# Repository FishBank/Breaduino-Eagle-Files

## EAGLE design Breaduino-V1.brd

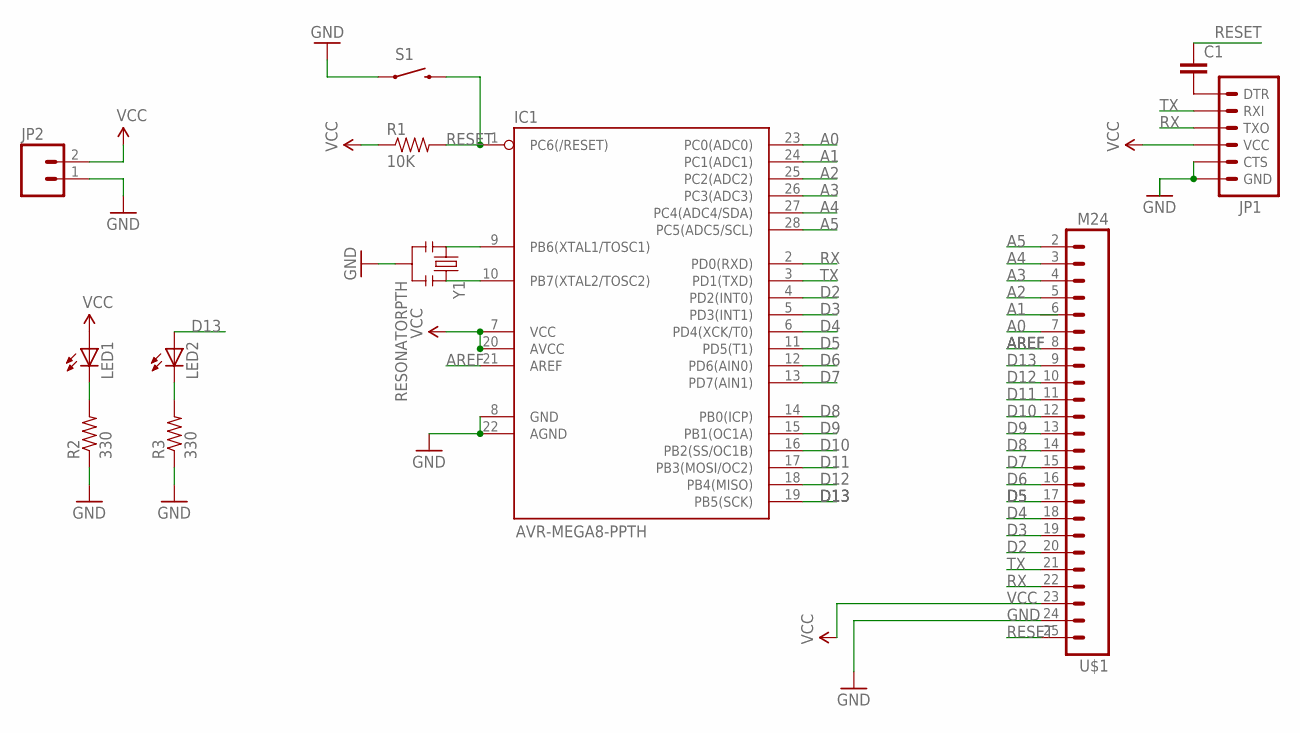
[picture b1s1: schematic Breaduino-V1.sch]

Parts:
C1: CAPPTH; CAP-PTH-SMALL
IC1: AVR-MEGA8-PPTH; DIL28-3
JP1: ARDUINO_SERIAL_PROGRAMPTH; 1X06
JP2: M02JST-PTH-2; JST-2-PTH
LED1, LED2: LED3MM
R1: 10K; AXIAL-0.3
R2, R3: 330; AXIAL-0.3
S1: SWITCH-MOMENTARY-2PTH; TACTILE-PTH
U$1: M24; 1X24
Y1: RESONATORPTH; RESONATOR-PTH

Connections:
A0: IC1.23 (PC0(ADC0)), U$1.7
A1: IC1.24 (PC1(ADC1))
A2: IC1.25 (PC2(ADC2)), U$1.5
A3: IC1.26 (PC3(ADC3)), U$1.4
A4: IC1.27 (PC4(ADC4/SDA)), U$1.3
A5: IC1.28 (PC5(ADC5/SCL)), U$1.2
AREF: IC1.21 (AREF), U$1.8
D2: IC1.4 (PD2(INT0)), U$1.20
D3: IC1.5 (PD3(INT1)), U$1.19
D4: IC1.6 (PD4(XCK/T0)), U$1.18
D5: IC1.11 (PD5(T1)), U$1.17
D6: IC1.12 (PD6(AIN0)), U$1.16
D7: IC1.13 (PD7(AIN1)), U$1.15
D8: IC1.14 (PB0(ICP)), U$1.14
D9: IC1.15 (PB1(OC1A)), U$1.13
D10: IC1.16 (PB2(SS/OC1B)), U$1.12
D11: IC1.17 (PB3(MOSI/OC2)), U$1.11
D12: IC1.18 (PB4(MISO)), U$1.10
D13: IC1.19 (PB5(SCK)), LED2.A, U$1.9
GND: IC1.8 (GND), JP1.5 (CTS), JP1.6 (GND), JP2.1, R2.P$1 (1), R3.P$1 (1), S1.1, U$1.24, Y1.2
unnamed: LED1.K (C), R2.P$2 (2)
unnamed: LED2.K (C), R3.P$2 (2)
unnamed: IC1.9 (PB6(XTAL1/TOSC1)), Y1.1
unnamed: IC1.10 (PB7(XTAL2/TOSC2)), Y1.3
unnamed: C1.2, JP1.1 (DTR)
RESET: C1.1, IC1.1 (PC6(/RESET)), R1.P$2 (2), S1.3 (2), U$1.25
RX: IC1.2 (PD0(RXD)), JP1.3 (TXO), U$1.22
TX: IC1.3 (PD1(TXD)), JP1.2 (RXI), U$1.21
VCC: IC1.7 (VCC), IC1.20 (AVCC), JP1.4 (VCC), JP2.2, LED1.A, R1.P$1 (1), U$1.23

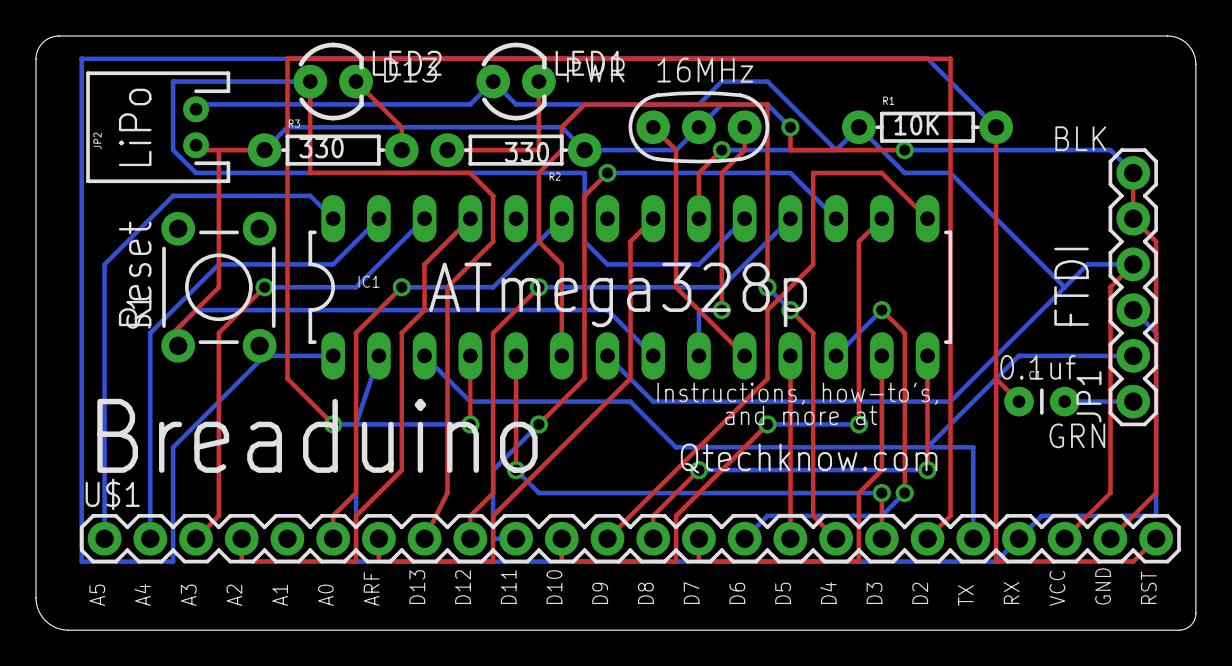
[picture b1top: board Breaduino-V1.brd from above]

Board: 2 copper layers, 64.4 x 33.0 mm, 12 parts (0 on the bottom side), 28 nets.

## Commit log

2012-07-13 Schematic

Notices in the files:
parts and their libraries:
SFE DigitalIC: Licensing: CC v3.0 Share-Alike You are welcome to use this library for commercial purposes.
